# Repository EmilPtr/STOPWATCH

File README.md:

# Stopwatch
This is a simple stopwatch PCB that was intended for me to get into the complex world of PCB design and microcontrollers on PCBs. It functions like a regular stopwatch, you cna start the timer, stop it, and reset it, and it has an accuracy to tens of miliseconds.

## Schematic

the schematic looks like this, it consists of several HC595 8-bit shift registers to multiplex the MCU's pins for minimal pin usage on displays, some buttons for control, and a 3.3V regulator to regulate a 3xAA battery's voltage to power the MCU in a stable fashion.

## PCB 

The PCB uses only 2 layers to be as cost effective as possible and stays within 100mm x 100mm to capitalize on JLCPCB's lowest cost threshold. It was designed in a way where traces of similar functionality are grouped together, but not close enough to be affected by other traces by Faraday's Law.

## Physical Build
YAYYY ITS DONE!!! :D
https://github.com/user-attachments/assets/ebe392f2-ca30-4a46-b4f1-2a95856c1f90

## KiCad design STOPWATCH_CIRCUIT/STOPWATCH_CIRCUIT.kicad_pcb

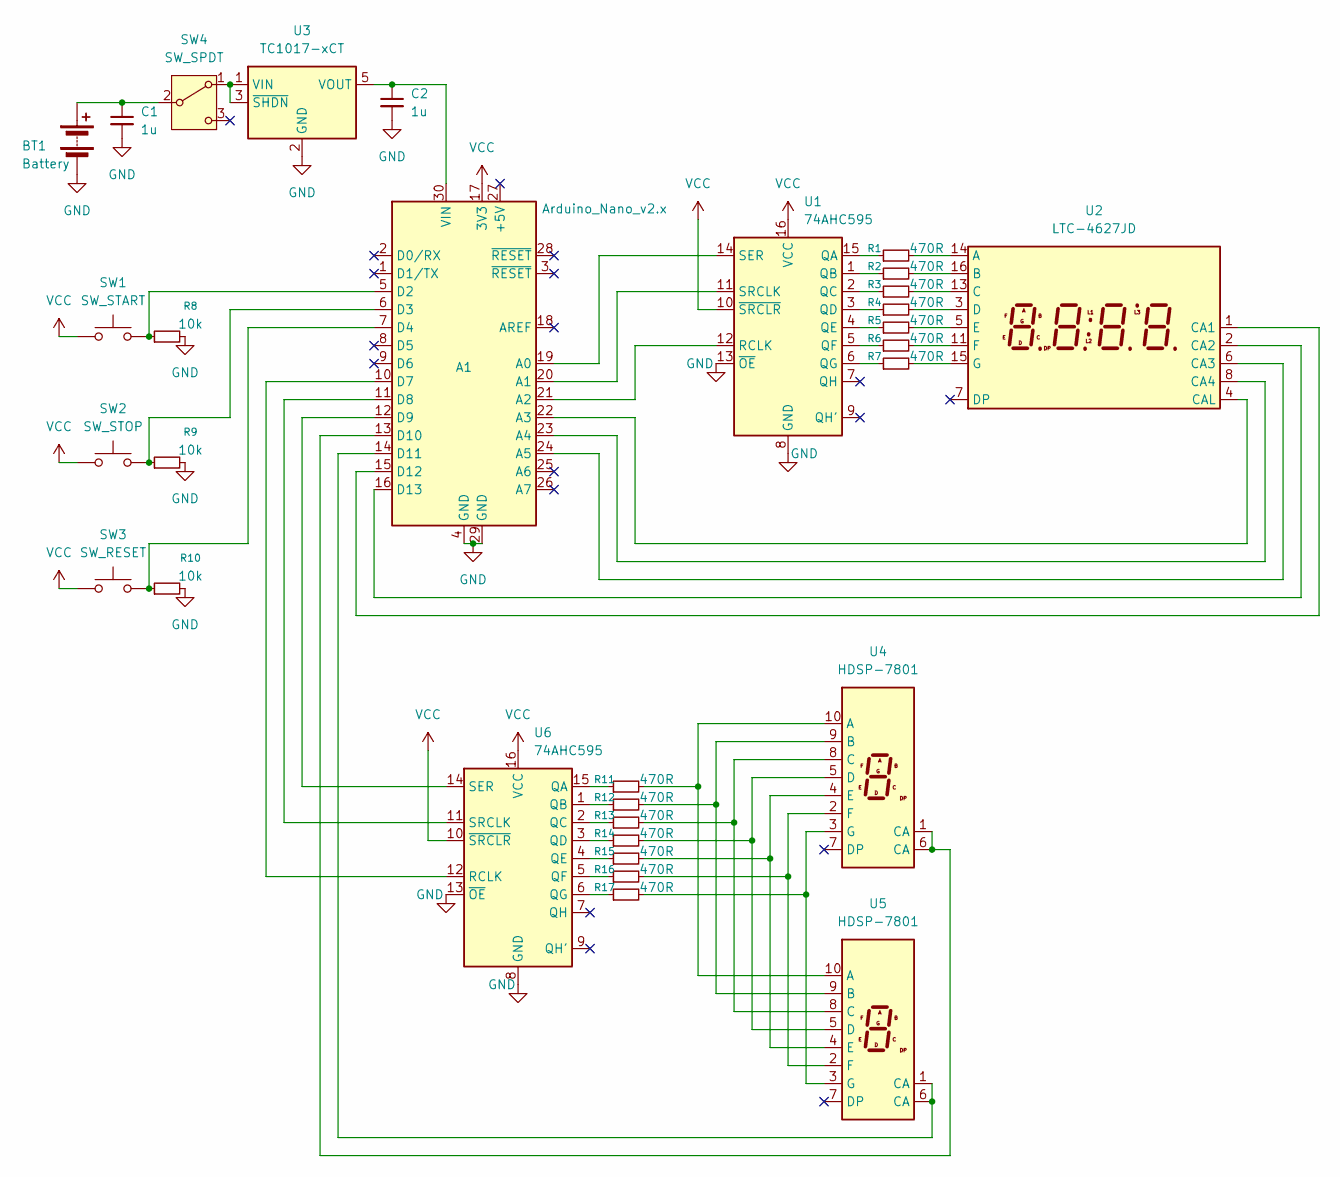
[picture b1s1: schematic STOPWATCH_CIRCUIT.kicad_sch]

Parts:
A1: Arduino_Nano_v2.x; Arduino_Nano
BT1: Battery; PinHeader_1x02_P2.54mm_Vertical
C1, C2: 1u; C_0805_2012Metric_Pad1.18x1.45mm_HandSolder
R1, R2, R3, R4, R5, R6, R7, R11, R12, R13, R14, R15, R16, R17: 470R; R_0805_2012Metric_Pad1.20x1.40mm_HandSolder
R8, R9, R10: 10k; R_0805_2012Metric_Pad1.20x1.40mm_HandSolder
SW1: SW_START; SW_Push_1P1T_NO_CK_KSC9xxG
SW2: SW_STOP; SW_Push_1P1T_NO_CK_KSC9xxG
SW3: SW_RESET; SW_Push_1P1T_NO_CK_KSC9xxG
SW4: SW_SPDT; SW_Slide_SPDT_Angled_CK_OS102011MA1Q
U1, U6: 74AHC595; SOIC-16_3.9x9.9mm_P1.27mm
U2: LTC-4627JD; LTC-4627Jx
U3: TC1017-xCT; SOT-23-5
U4, U5: HDSP-7801

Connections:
GND: A1.4 (GND), A1.29 (GND), BT1.2 (-), C1.2, C2.2, R8.2, R9.2, R10.2, U1.8 (GND), U1.13 (~OE), U3.2 (GND), U6.8 (GND), U6.13 (~OE)
unnamed: A1.19 (A0), U1.14 (SER)
unnamed: A1.20 (A1), U1.11 (SRCLK)
unnamed: A1.21 (A2), U1.12 (RCLK)
unnamed: A1.22 (A3), U2.4 (CAL)
unnamed: A1.23 (A4), U2.8 (CA4)
unnamed: A1.24 (A5), U2.6 (CA3)
unnamed: A1.5 (D2), R8.1, SW1.2
unnamed: A1.6 (D3), R9.1, SW2.2
unnamed: A1.7 (D4), R10.1, SW3.2
unnamed: A1.10 (D7), U6.12 (RCLK)
unnamed: A1.11 (D8), U6.11 (SRCLK)
unnamed: A1.12 (D9), U6.14 (SER)
unnamed: A1.13 (D10), U4.1 (CA), U4.6 (CA)
unnamed: A1.14 (D11), U5.1 (CA), U5.6 (CA)
unnamed: A1.15 (D12), U2.1 (CA1)
unnamed: A1.16 (D13), U2.2 (CA2)
unnamed: A1.30 (VIN), C2.1, U3.5 (VOUT)
unnamed: BT1.1 (+), C1.1, SW4.2 (B)
unnamed: SW4.1 (A), U3.1 (VIN), U3.3 (~SHDN)
unnamed: R1.1, U1.15 (QA)
unnamed: R2.1, U1.1 (QB)
unnamed: R3.1, U1.2 (QC)
unnamed: R4.1, U1.3 (QD)
unnamed: R5.1, U1.4 (QE)
unnamed: R6.1, U1.5 (QF)
unnamed: R7.1, U1.6 (QG)
unnamed: R1.2, U2.14 (A)
unnamed: R2.2, U2.16 (B)
unnamed: R3.2, U2.13 (C)
unnamed: R4.2, U2.3 (D)
unnamed: R5.2, U2.5 (E)
unnamed: R6.2, U2.11 (F)
unnamed: R7.2, U2.15 (G)
unnamed: R11.2, U4.10 (A), U5.10 (A)
unnamed: R12.2, U4.9 (B), U5.9 (B)
unnamed: R13.2, U4.8 (C), U5.8 (C)
unnamed: R14.2, U4.5 (D), U5.5 (D)
unnamed: R15.2, U4.4 (E), U5.4 (E)
unnamed: R16.2, U4.2 (F), U5.2 (F)
unnamed: R17.2, U4.3 (G), U5.3 (G)
unnamed: R11.1, U6.15 (QA)
unnamed: R12.1, U6.1 (QB)
unnamed: R13.1, U6.2 (QC)
unnamed: R14.1, U6.3 (QD)
unnamed: R15.1, U6.4 (QE)
unnamed: R16.1, U6.5 (QF)
unnamed: R17.1, U6.6 (QG)
VCC: A1.17 (3V3), SW1.1, SW2.1, SW3.1, U1.10 (~SRCLR), U1.16 (VCC), U6.10 (~SRCLR), U6.16 (VCC)

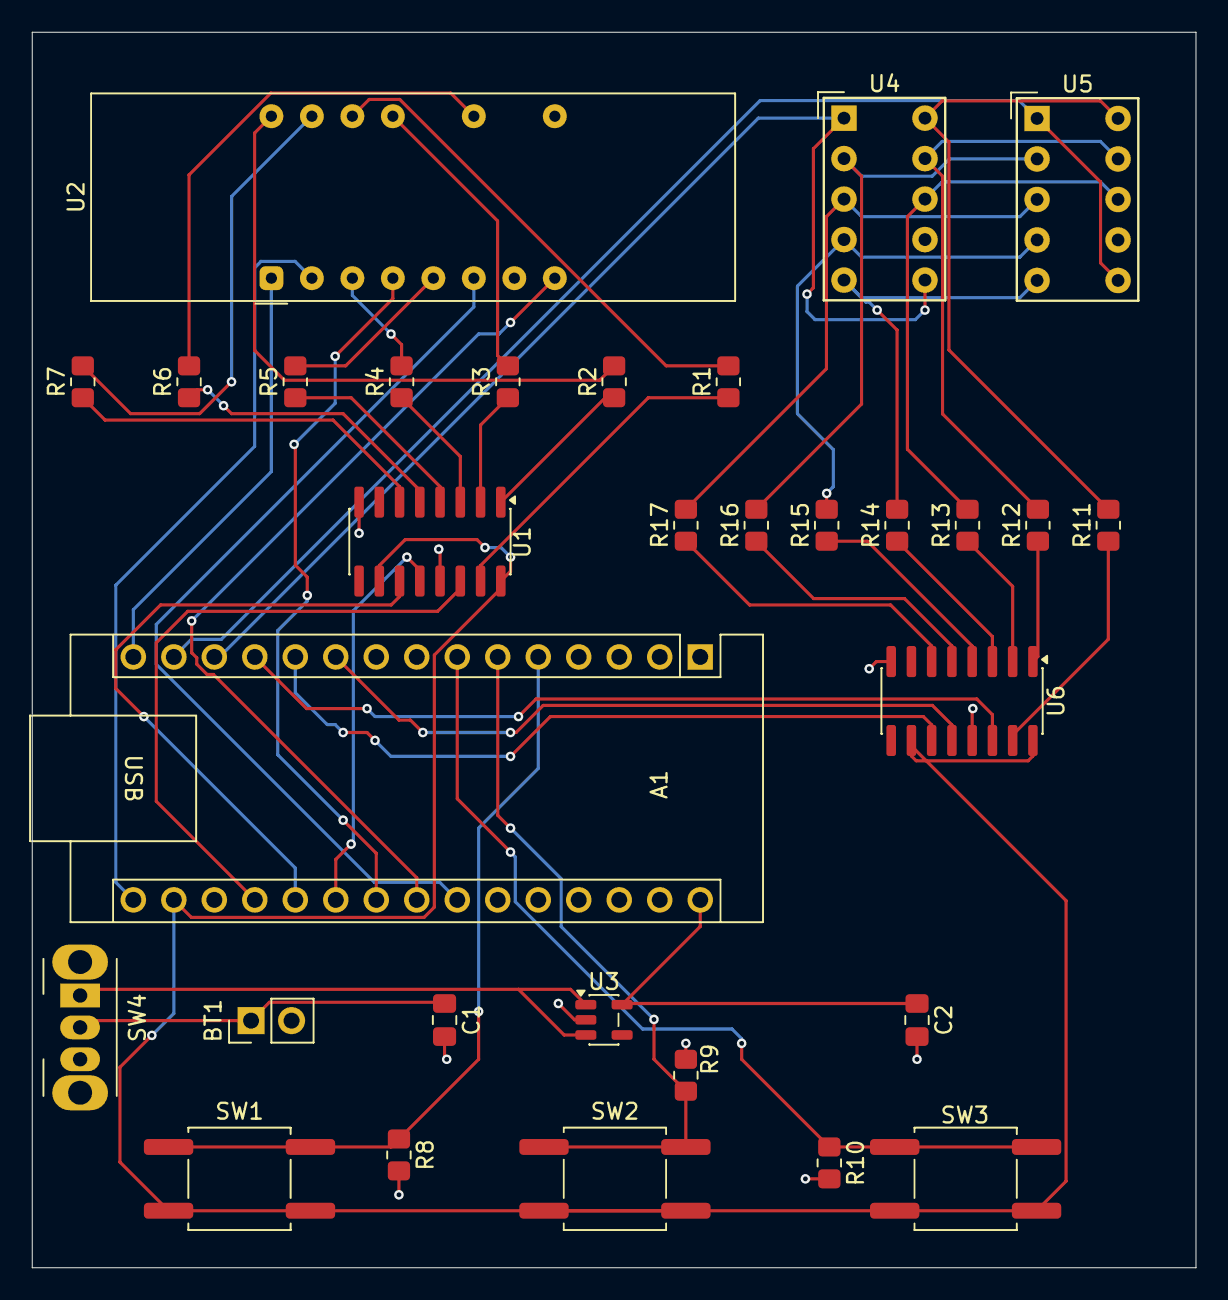
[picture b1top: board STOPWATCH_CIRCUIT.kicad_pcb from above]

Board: 2 copper layers, 73.0 x 77.5 mm, 31 parts (0 on the bottom side), 49 nets.

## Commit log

2026-03-09 Finished design schematic and PCB
2026-03-11 Finished adding the 2 extra digits for miliseconds and redid the whole board
2026-03-11 Finalized design
2026-03-17 Made README.md
2026-04-16 Update README with project completion announcement
    Added completion message and link to assets.
2026-04-16 Add main Arduino firmware for timer functionality
